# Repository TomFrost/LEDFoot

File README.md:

# LEDFoot

Control board for WS2815 and other 3-4 pin individually addressable LED strips that operate at 12V. Drivable by various inexpensive ESP32 dev boards. KiCad.

## Features

* 12V input, 8A max rating
* Sound-reactive support with onboard mic
* Wide range of ESP32 dev board support
  * ESP32-S3 (audio reactive **supported**)
    * ESP32-S3 Super Mini [[Info](https://www.espboards.dev/esp32/esp32-s3-super-mini/)] [[Aliexpress](https://www.aliexpress.us/item/3256807337822466.html)]
    * Seeed Studio XIAO ESP32S3 [[Info](https://wiki.seeedstudio.com/xiao_esp32s3_getting_started/)] [[Aliexpress](https://www.aliexpress.us/item/3256807240469656.html)]
  * ESP32-C3 (audio-reactive **not supported**)
    * ESP32-C3 Super Mini [[Info](https://wiki.icbbuy.com/doku.php?id=developmentboard:esp32-c3mini#schematic)] [[Aliexpress](https://www.aliexpress.us/item/3256806846231704.html)]
    * Seeed Studio XIAO ESP32C3 [[Info](https://wiki.seeedstudio.com/XIAO_ESP32C3_Getting_Started/)] [[Aliexpress](https://www.aliexpress.us/item/3256806641821574.html)]
  * Potentially more: Any board with 14-18 pins and 5V, GND, 3.3V to the RIGHT of the USB port may be compatible.
    * Waveshare Zero boards are not compatible: their power pins are on the left side.
* Reverse polarity protection
* Transient power spike protection
* Over-voltage and over-amperage protection
* Power-save mode when lights are off
* Ample onboard capacitance to reduce flicker and power overdraw
* 5V data signal
* 12 breakout pins for customizations, including 5 power pins: 12V, 5V, 3.3V, Ground, and Switched Ground (disconnects when LEDs are off)
* 3.3V, 5V, 12V, and GND breakout pins
* Tactile button
* Configurable data line
* Supports WLED and any other software that can be flashed to the ESP32-C3

## Revisions

### rev 2 (2025-02) (Super Mini Board footprint version)

#### Changes

* Made 5V buck converter corrections outlined in rev 1
* Corrected RUEF800 fuse footprint, kept on the back of the board
* Switched from through-hole headers to SMD headers to avoid puncturing RUEF800
* Added on-board SMD microphone for sound-reactivity
* Reduced buttons to 1. Figuring out which of those two little buttons you had your finger on was terrible if the board was mounted out of sight.
* Added a high-current logic-level MOSFET as a non-mechanical relay to shut off power to the LED strip when off, saving significant energy.

#### Status

* Printed and not fully tested
* Onboard mic works wonderfully when the ESP32 daughterboard is powered via USB, but not 12V. This is due to too much ripple on the 5V rail. There are a few potential reasons for this; the largest was the decision to leave COMP on the MP1584EN floating to save space. This didn't cause an issue until adding the PDM mic, which is very sensitive to this noise. Its signal is nearly always high as a result.

#### Bonus assembly video

[Click to watch](https://www.youtube.com/watch?v=fRJq4f_MXR0)

### rev 1 (2025-01) (WeAct Studio ESP32-C3Fx4 version)

#### Intended Features

* Powered by the [WeAct Studio ESP32-C3Fx4](https://github.com/WeActStudio/WeActStudio.ESP32C3CoreBoard?tab=readme-ov-file)
family of development boards
* 12V input, 8A max rating
* Reverse polarity protection
* Transient power spike protection
* Over-voltage and over-amperage protection
* Ample onboard capacitance to reduce flicker and power overdraw
* 5V data signal
* Breakout pins for GPIOs 0-7 of the ESP32-C3, including 6 analog pins
* 3.3V, 5V, 12V, and GND breakout pins
* Two tactile buttons (GPIO 8 and 9)
* Configurable data line on GPIO 10
* Supports WLED and any other software that can be flashed to the ESP32-C3

#### Status

Printed and functional, with assembly modifications. Assembling as-is results in a damaged resistor (R2) and
non-functional buck converter circuit that fails to power the ESP32 board.

#### Required modifications

1. An additional SS34 Schottky diode (same as D2) must be wired reverse-biased from GND to the input side of the L1
  Inductor. There is space for this on the right side of L1, connecting to the left side of C6. Solder bridges are easy
here.
2. A resistor (Ideally 100k Ohms, but any in the 10k - 250k range will work) must be connected between pin 5 (GND) and
   pin 6 (FREQ) of the MP1584EN chip (U1). This is easy to place directly on the pads for these two pins, because they
are adjacent on the right side of the chip.
3. The voltage divider resistors for the MP1584EN chip, R3 and R4, are not properly configured to supply 5V. There are
   many solutions to this. With an already-assembled board and only with access to the original BOM, I solved it by
adding a 4.7k resistor in parallel with the R3 3.3k resistor, simply by soldering to the same R3 pads. They are large
enough to accommodate both resistors side by side. This results in an approx 4.8V output, which is sufficient.
4. Remove the R2 resistor, which leaves the EN pin of the MP1584EN chip (U1) floating. Per the data sheet, this is fine
   as EN is pulled up internally. Note that this is not confirmed to be a hard requirement, however this resistor did
burn out without the modifications above.
5. The footprint of the RUEF800 fuse (F1) is larger than the board allows. To accomodate, mount this fuse to the
   underside of the board, bending the legs so that it can lay flat, parallel to the board. Allow space for
ventillation, and ensure that any case or mounting solution used does not apply pressure to the fuse or damage it
against the legs of the other through-hole components. Solder the legs on both sides of the board, as this is
a high-current component that requires an extremely secure connection.

## Disclaimer

I am a self-taught hobbyist, not a credentialed electrical engineer. Voltage and current ratings are theoretical and
not thoroughly tested in a lab environment. I am not liable for any use of these designs, derivations of these designs,
or any destruction of property or loss of life that may result. Use of these designs is prohibited, and any choice to
do otherwise is made at your own risk.

## License

These designs are published as an educational tool only. The designs, as well as any part manufactured according to
these designs or a derivation thereof, may not be modified, produced, sold, or used as part of another design or
product. These designs are wholly owned by their creator, with all applicable rights reserved.

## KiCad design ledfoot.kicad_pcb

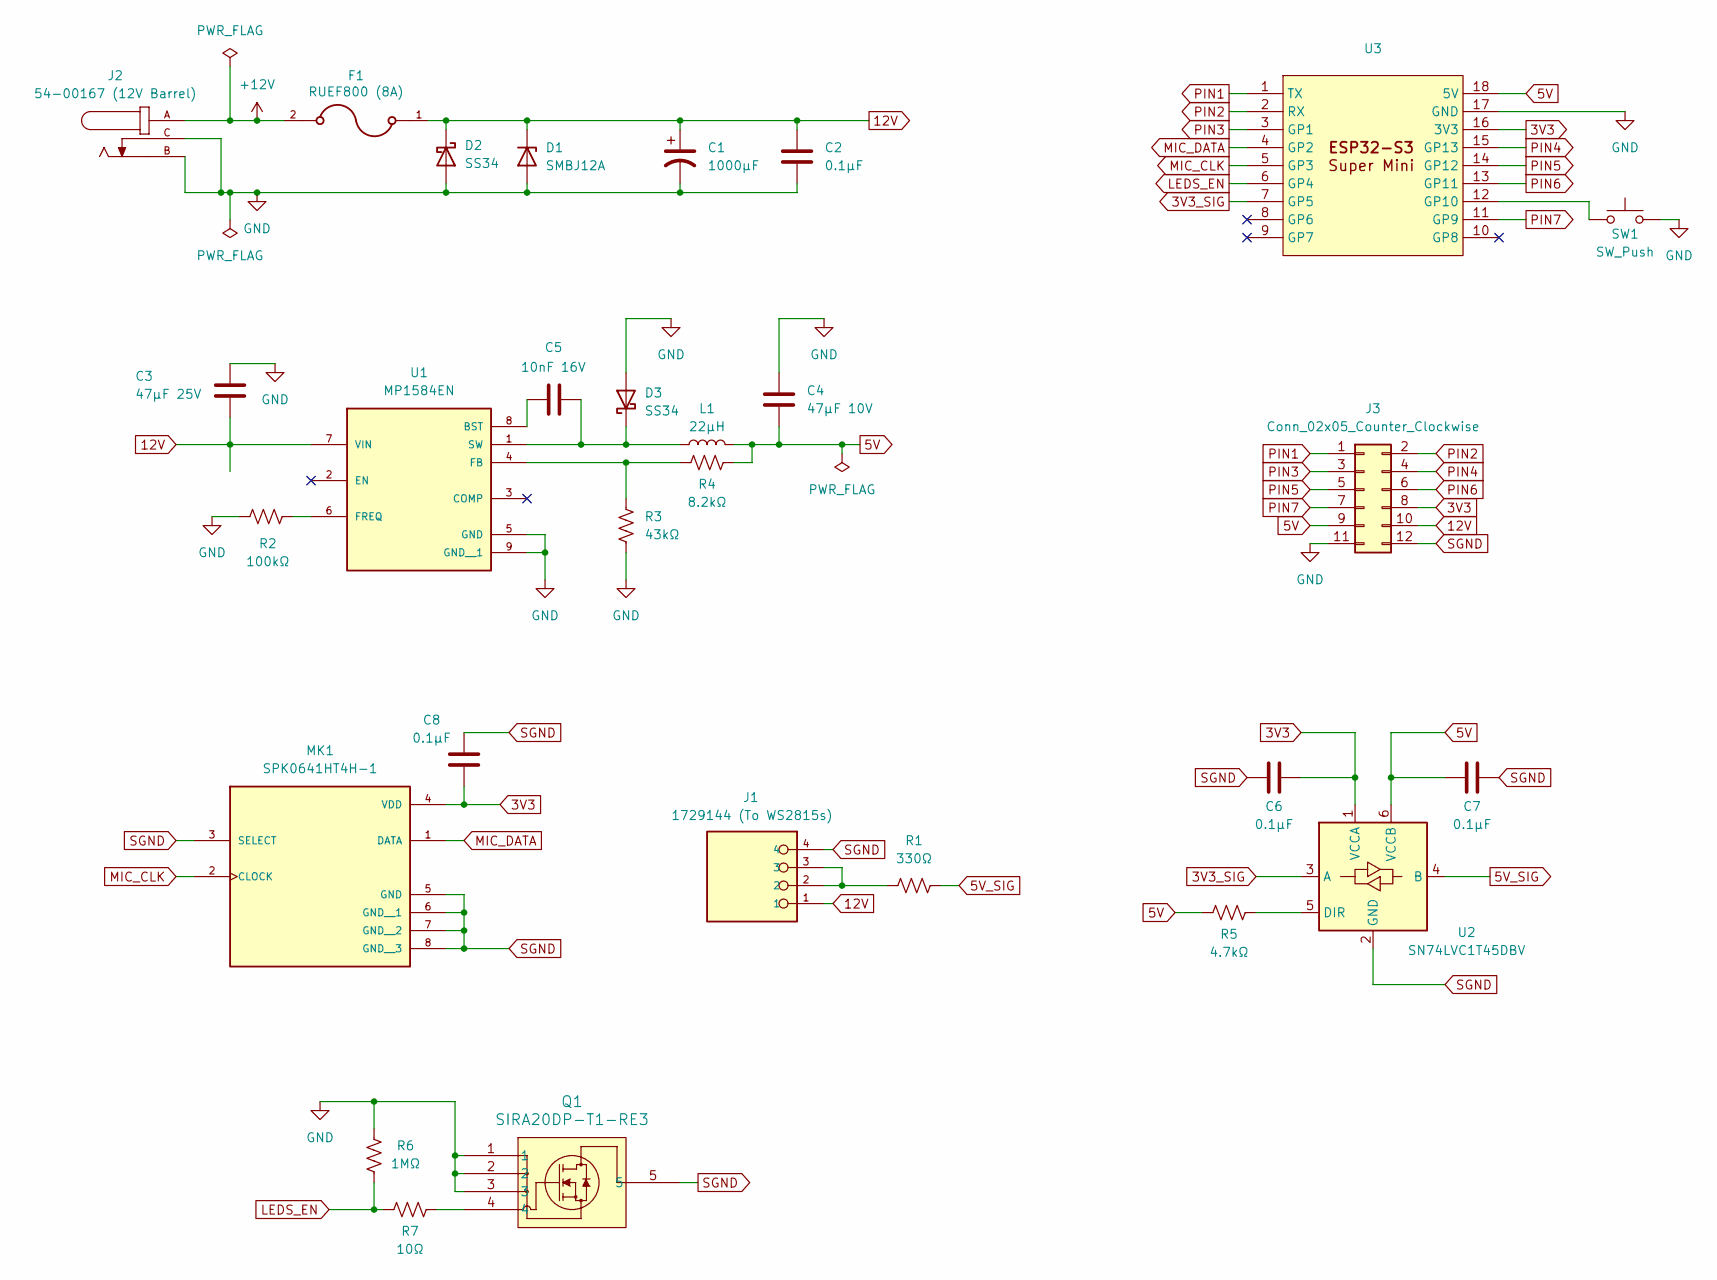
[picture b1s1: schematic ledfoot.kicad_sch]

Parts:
C1: 1000µF; CP_Radial_D8.0mm_P3.50mm
C2: 0.1µF; C_0603_1608Metric; Part GRM188R72A104KA35D
C3: 47µF 25V; C_0603_1608Metric
C4: 47µF 10V; C_0603_1608Metric
C5: 10nF 16V; C_0603_1608Metric
C6, C7, C8: 0.1µF; C_0603_1608Metric
D1: SMBJ12A; D_SMB
D2, D3: SS34; D_SMA
F1: RUEF800 (8A); FUSE_RUEF800
J1: 1729144 (To WS2815s); PHOENIX_1729144
J2: 54-00167 (12V Barrel); TENSILITY_54-00167; PARTREV A
J3: Conn_02x05_Counter_Clockwise; PinHeader_2x06_P2.54mm_Vertical_SMD
L1: 22µH; L_APV_ANR4018
MK1: SPK0641HT4H-1; MIC_SPK0641HT4H-1; PARTREV C
Q1: SIRA20DP-T1-RE3; POWERPAK_SO-8_SINGLE_VIS
R1: 330Ω; R_0603_1608Metric
R2: 100kΩ; R_0603_1608Metric
R3: 43kΩ; R_0603_1608Metric
R4: 8.2kΩ; R_0603_1608Metric
R5: 4.7kΩ; R_0603_1608Metric
R6: 1MΩ; R_0603_1608Metric
R7: 10Ω; R_0603_1608Metric
SW1: SW_Push; SW_SPST_PTS645
U1: MP1584EN; SOIC127P600X170-9N
U2: SN74LVC1T45DBV; SOT-23-6
U3: Tenstar-ESP32-S3-SuperMini-EdgeOnly

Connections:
3V3: C6.1, C8.1, J3.8, MK1.4 (VDD), U2.1 (VCCA), U3.16 (3V3)
3V3_SIG: U2.3 (A), U3.7 (GP5)
5V: C4.2, C7.1, J3.9, L1.2, R4.2, R5.1, U2.6 (VCCB), U3.18 (5V)
5V_SIG: R1.2, U2.4 (B)
12V: C1.1, C2.1, C3.2, D1.1 (K), D2.1 (K), F1.1, J1.1, J3.10, U1.7 (VIN)
+12V: F1.2, J2.A
GND: C1.2, C2.2, C3.1, C4.1, D1.2 (A), D2.2 (A), D3.2 (A), J2.B, J2.C, J3.11, Q1.1, Q1.2, Q1.3, R2.1, R3.2, R6.2, SW1.2, U1.5 (GND), U1.9 (GND__1), U3.17 (GND)
LEDS_EN: R6.1, R7.1, U3.6 (GP4)
MIC_CLK: MK1.2 (CLOCK), U3.5 (GP3)
MIC_DATA: MK1.1 (DATA), U3.4 (GP2)
unnamed: C5.2, D3.1 (K), L1.1, U1.1 (SW)
unnamed: J1.2, J1.3, R1.1
unnamed: Q1.4, R7.2
unnamed: C5.1, U1.8 (BST)
unnamed: R3.1, R4.1, U1.4 (FB)
unnamed: R2.2, U1.6 (FREQ)
unnamed: R5.2, U2.5 (DIR)
unnamed: SW1.1, U3.12 (GP10)
PIN1: J3.1, U3.1 (TX)
PIN2: J3.2, U3.2 (RX)
PIN3: J3.3, U3.3 (GP1)
PIN4: J3.4, U3.15 (GP13)
PIN5: J3.5, U3.14 (GP12)
PIN6: J3.6, U3.13 (GP11)
PIN7: J3.7, U3.11 (GP9)
SGND: C6.2, C7.2, C8.2, J1.4, J3.12, MK1.3 (SELECT), MK1.5 (GND), MK1.6 (GND__1), MK1.7 (GND__2), MK1.8 (GND__3), Q1.5, U2.2 (GND)

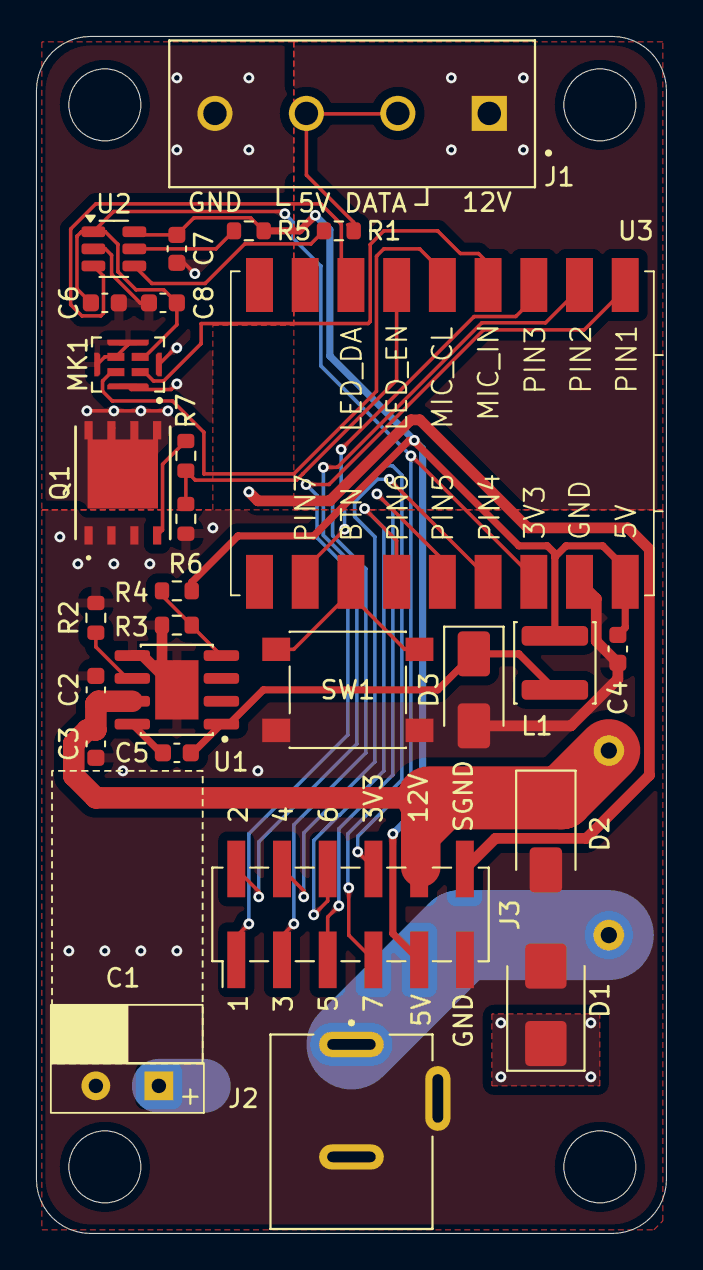
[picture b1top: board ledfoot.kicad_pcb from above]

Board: 2 copper layers, 35.0 x 66.5 mm, 29 parts (1 on the bottom side), 26 nets.

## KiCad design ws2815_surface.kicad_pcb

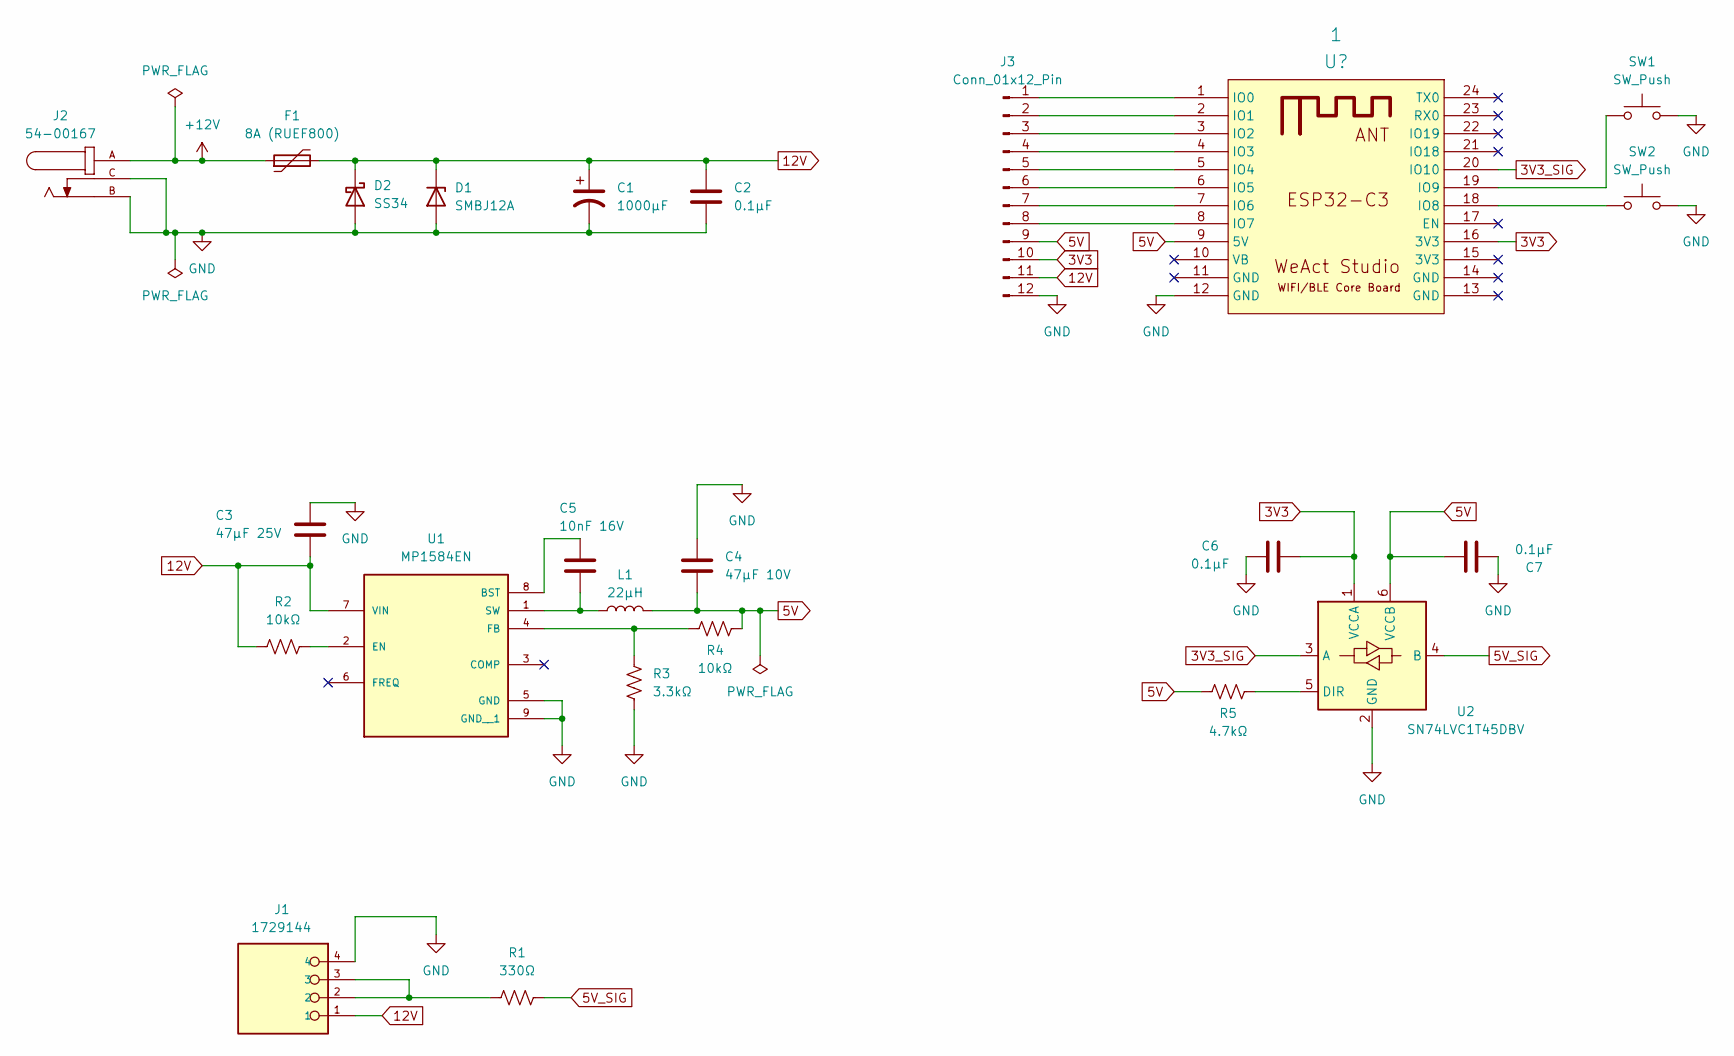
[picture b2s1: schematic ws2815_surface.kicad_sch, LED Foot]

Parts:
1: U?; WeAct-ESP32C3CoreBoard
C1: 1000µF; CP_Radial_D10.0mm_P5.00mm
C2: 0.1µF; C_0603_1608Metric; Part GRM188R72A104KA35D
C3: 47µF 25V; C_0805_2012Metric
C4: 47µF 10V; C_0805_2012Metric
C5: 10nF 16V; C_0805_2012Metric
C6, C7: 0.1µF; C_0603_1608Metric
D1: SMBJ12A; D_SMB
D2: SS34; D_SMA
F1: 8A (RUEF800); FUSRR505W81L660T250H1360
J1: 1729144; PHOENIX_1729144
J2: 54-00167; TENSILITY_54-00167; PARTREV A
J3: Conn_01x12_Pin; PinHeader_1x12_P2.54mm_Vertical
L1: 22µH; L_APV_ANR4018
R1: 330Ω; R_0805_2012Metric
R2, R4: 10kΩ; R_0805_2012Metric
R3: 3.3kΩ; R_0805_2012Metric
R5: 4.7kΩ; R_0805_2012Metric
SW1, SW2: SW_Push; SW_SPST_PTS645
U1: MP1584EN; SOIC127P600X170-9N
U2: SN74LVC1T45DBV; SOT-23-6

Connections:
3V3: 1.16 (3V3), C6.1, J3.10, U2.1 (VCCA)
3V3_SIG: 1.20 (IO10), U2.3 (A)
5V: 1.9 (5V), C4.2, C7.1, J3.9, L1.2, R4.2, R5.1, U2.6 (VCCB)
5V_SIG: R1.2, U2.4 (B)
12V: C1.1, C2.1, C3.2, D1.1 (K), D2.1 (K), F1.2, J1.1, J3.11, R2.1, U1.7 (VIN)
+12V: F1.1, J2.A
GND: 1.12 (GND), C1.2, C2.2, C3.1, C4.1, C6.2, C7.2, D1.2 (A), D2.2 (A), J1.4, J2.B, J2.C, J3.12, R3.2, SW1.2, SW2.2, U1.5 (GND), U1.9 (GND__1), U2.2 (GND)
unnamed: 1.1 (IO0), J3.1
unnamed: 1.2 (IO1), J3.2
unnamed: 1.3 (IO2), J3.3
unnamed: 1.4 (IO3), J3.4
unnamed: 1.5 (IO4), J3.5
unnamed: 1.6 (IO5), J3.6
unnamed: 1.7 (IO6), J3.7
unnamed: 1.8 (IO7), J3.8
unnamed: 1.18 (IO8), SW2.1
unnamed: 1.19 (IO9), SW1.1
unnamed: J1.2, J1.3, R1.1
unnamed: C5.1, U1.8 (BST)
unnamed: R2.2, U1.2 (EN)
unnamed: R3.1, R4.1, U1.4 (FB)
unnamed: C5.2, L1.1, U1.1 (SW)
unnamed: R5.2, U2.5 (DIR)

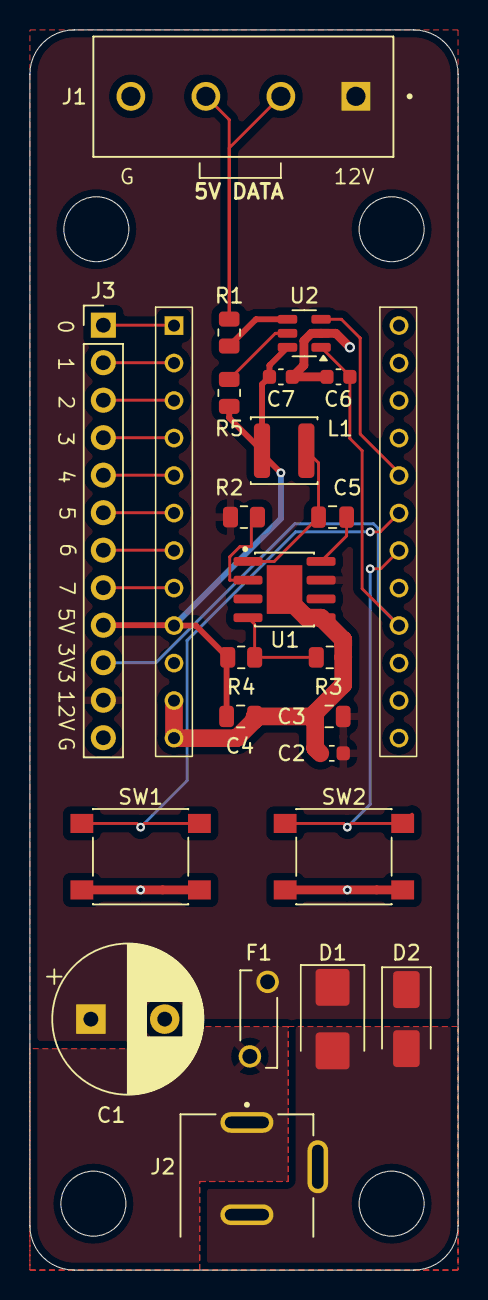
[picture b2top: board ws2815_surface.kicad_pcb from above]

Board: 2 copper layers, 29.0 x 84.0 mm, 24 parts (0 on the bottom side), 23 nets.

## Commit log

2025-01-30 Add rev1
2025-02-05 Correct project naming
2025-02-13 Revision 2 ready for production
2025-02-25 Fix MP1584EN voltage divider swap
2025-02-28 Add rev2 docs
2025-02-28 Add rev2 assembly video
